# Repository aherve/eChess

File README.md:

# eChess: play online chess, but over the board

https://github.com/user-attachments/assets/bde2e431-92bb-4959-bb7b-e80072c71205

_Demo game against a lichess bot. The phone showcases the game for demo purposes, but isn't actually required to play_

## How it works

- The board is equipped with 64 hall effect sensors, and 64 LEDs.
- The board can communicate via usb to a nodejs program that runs on an embedded raspberry PI with touchscreen
- The program can communicate with both lichess API and the physical board

### Piece detection

The general principle is to hide magnetic hall effect sensors under the board to detect piece presence. White & black pieces have a hidden magnet in them, in different orientations, respectively

Using linear sensors we are then able to detect between 3 distinct states:

- white piece (low voltage)
- black piece (high voltage)
- no piece (~ half the supply voltage)

In addition to the sensors, a 8x8 LED matrix is used to display the opponent's moves on the board. An arduino microcontroller interfaces with an embedded go program to control the LEDs, read the sensors, and communicate with the lichess API.

## Showing the moves

Each square is equipped with a blue LED that can be lit to signal the opponent's move. It's bright enough that we don't miss a move, and discreet enough that it doesn't distract from the game.

## The electronics

For the board to work, is is necessary to:

- read inputs from the program, and light any combination of leds on a 8x8 grid
- read the state of 64 hall effect sensors in near real time, and send the state to the program whenever a change is detected

Since the arduino has a limited number of pins, two 74HC595 shift registers are used to control the LEDs with multiplexing, and an additional 74HC4051 multiplexer is used to control the sensor rows. Each of the sensor outputs are connected to one of the analog inputs of the microcontroller (arduino conveniently has 8 of them).

### The sensor matrix

According to their spreadsheet, the power-on time of the the hall sensors is somewhere from 175μs to 300μs. This is slow enough that we can't use multiplexing to power the sensors. Instead I went for a 8x8 matrix where all of the sensors are always powered. Their input readings are then selected using some BJT transistors whose switch time is in the order of 30ns (so about 8 500 times faster than the sensors power-on time)

<figure>

<figcaption>Details of the sensor matrix, only 4 sensors are shown. Sending <i>QA=1</i>, <i>QB=0</i> and reading <i>A1</i> input would provide a reading of the bottom-right sensor of this diagram</figcaption>
</figure>

### Electronics overview

The three 74HC595 shift registers are chained, and connected to the arduino as follows(only 4 sensors are shown for simplicity):

_complete overview of the electronics. Full kiCad files can be found in the [kiCad](kiCad) directory_

With this setup, [the microcontroller](arduino/arduino.ino) can use multiplexing to control the LEDs and read the sensors in near real time, while using very few pins from the microcontroller.

### The final build

For the build I soldered 64 leds, hall effect sensors, and transistors directly to a wooden board I build and painted. The shift-register ICs are wired to the microcontroller thanks to a custom PCB [ whose files can be found here ](eBoard_pcb)

_soldered pcb with arduino nano, IC sockets and some connectors_

_internal view of the board_

_closeup of the pcb after installation_

## Microconctroller setup

Arduino nano is used. It's cheap, small, and conveniently has 8 analog inputs, which is perfect for this use case.

## workflow

The arduino loop does the following:

1. **Read all the sensors**

   Using multiplexing, read all states from the 64 hall sensors and build a board state from it. If a state change is detected, then we serialize the board state and send it to the computer.

2. **Read the LED input state**

   Read from usb and set the desired LED state

3. **Display the LEDs**

   For each lit LED from the input state, light the corresponding LED on the board, wait 2ms, and turn it off.

Since we are multiplexing the display, the entire loop needs to be _fast_. Fast enough that you don't see any flickering while we are reading 64 sensors and communicating via USB between each LED blink.

## Serializing the position

A chess board has a very convenient size of 8x8, which allows to represent a row with exactly two bytes:

- first byte signals positions of white pieces on row _a_
- second byte signals positions of black pieces on row _a_
- third byte signals positions of white pieces on row _b_
- ...etc until 16 bytes are sent to fully represent the board
- at the end of a serialization, three 255 bytes are sent to signal the end of the transmission. Since (255, 255, 255) would represent at least one row filled with both white _and_ black pieces, there is no ambiguity in the transmission.

This protocol allows the board to send partial states between led blinks, which removes any flickering from the display. The program can wait for a (255, 255, 255) sequence to know that the board state is fully transmitted, and in case of data corruption, it can ignore a broken state, and start over everytime a (255, 255, 255) sequence is detected.

_Example of how a row with 2 white pieces and 1 black piece would be encoded_

## The program

Lastly, the main program is written in go, and communicates with the arduino. It will read both the board state and the game moves from lichess to reconcilate the position, and determine when a move should be played (_i.e._ sent to the server), or when some LEDs should be lit. The user interface is provided by a touchscreen, and everything runs on a raspberry zero.

The code can be found in [the app directory](goapp/)

## Conclusion

I've been playing with this board for quite a while now, and it has been a tremendous experience so far. It's definitely not suited for fast time controls, but lichess only provide their real-time API for rapid & classical time-controls anyway (has to do with anti-cheating measures I believe).

Playing lichess games while looking at a physical board is a delight, and has become my main way of playing chess at home.

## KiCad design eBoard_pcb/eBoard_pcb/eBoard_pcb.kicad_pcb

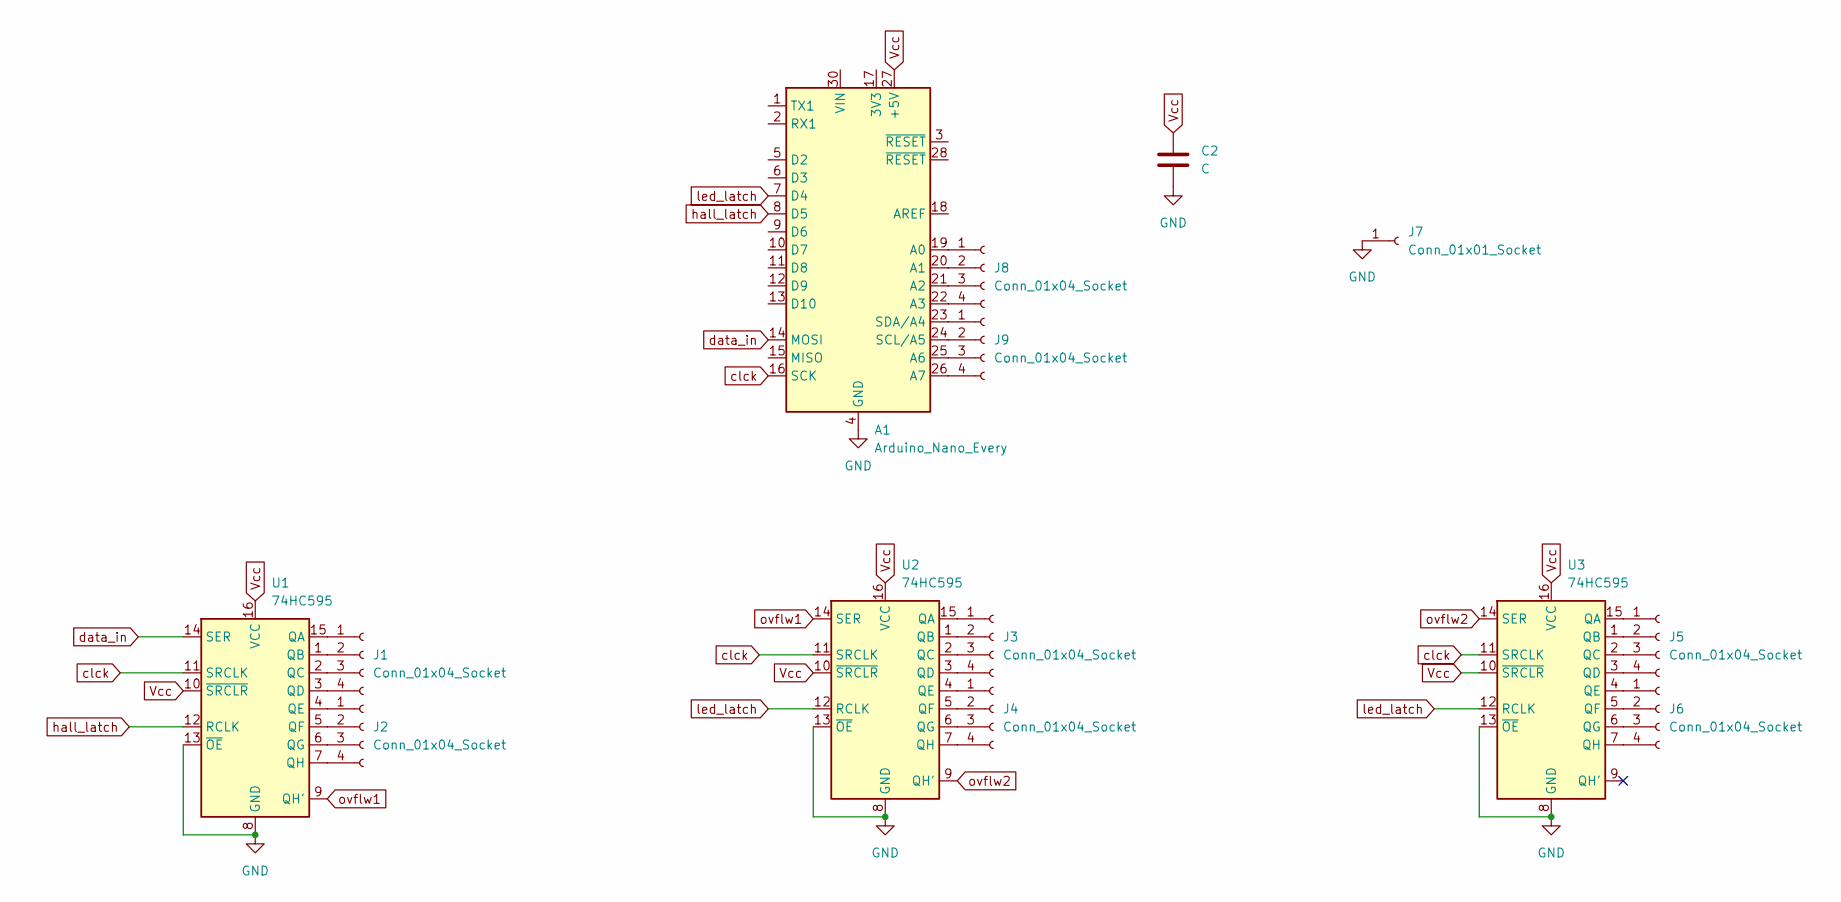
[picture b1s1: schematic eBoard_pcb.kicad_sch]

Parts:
A1: Arduino_Nano_Every; Arduino_Nano
C2: C; C_Disc_D3.8mm_W2.6mm_P2.50mm
J1, J2, J3, J4, J5, J6, J8, J9: Conn_01x04_Socket; JST_PH_B4B-PH-K_1x04_P2.00mm_Vertical
J7: Conn_01x01_Socket; PinHeader_1x01_P2.54mm_Horizontal
U1, U2, U3: 74HC595; DIP-16_W7.62mm_Socket

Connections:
GND: A1.4 (GND), A1.29 (GND), C2.2, J7.1, U1.8 (GND), U1.13 (~OE), U2.8 (GND), U2.13 (~OE), U3.8 (GND), U3.13 (~OE)
unnamed: A1.19 (A0), J8.1
unnamed: A1.20 (A1), J8.2
unnamed: A1.21 (A2), J8.3
unnamed: A1.22 (A3), J8.4
unnamed: A1.25 (A6), J9.3
unnamed: A1.26 (A7), J9.4
unnamed: A1.24 (SCL/A5), J9.2
unnamed: A1.23 (SDA/A4), J9.1
unnamed: J1.1, U1.15 (QA)
unnamed: J1.2, U1.1 (QB)
unnamed: J1.3, U1.2 (QC)
unnamed: J1.4, U1.3 (QD)
unnamed: J2.1, U1.4 (QE)
unnamed: J2.2, U1.5 (QF)
unnamed: J2.3, U1.6 (QG)
unnamed: J2.4, U1.7 (QH)
unnamed: J3.1, U2.15 (QA)
unnamed: J3.2, U2.1 (QB)
unnamed: J3.3, U2.2 (QC)
unnamed: J3.4, U2.3 (QD)
unnamed: J4.1, U2.4 (QE)
unnamed: J4.2, U2.5 (QF)
unnamed: J4.3, U2.6 (QG)
unnamed: J4.4, U2.7 (QH)
unnamed: J5.1, U3.15 (QA)
unnamed: J5.2, U3.1 (QB)
unnamed: J5.3, U3.2 (QC)
unnamed: J5.4, U3.3 (QD)
unnamed: J6.1, U3.4 (QE)
unnamed: J6.2, U3.5 (QF)
unnamed: J6.3, U3.6 (QG)
unnamed: J6.4, U3.7 (QH)
Vcc: A1.27 (+5V), C2.1, U1.10 (~SRCLR), U1.16 (VCC), U2.10 (~SRCLR), U2.16 (VCC), U3.10 (~SRCLR), U3.16 (VCC)
clck: A1.16 (SCK), U1.11 (SRCLK), U2.11 (SRCLK), U3.11 (SRCLK)
data_in: A1.14 (MOSI), U1.14 (SER)
hall_latch: A1.8 (D5), U1.12 (RCLK)
led_latch: A1.7 (D4), U2.12 (RCLK), U3.12 (RCLK)
ovflw1: U1.9 (QH'), U2.14 (SER)
ovflw2: U2.9 (QH'), U3.14 (SER)

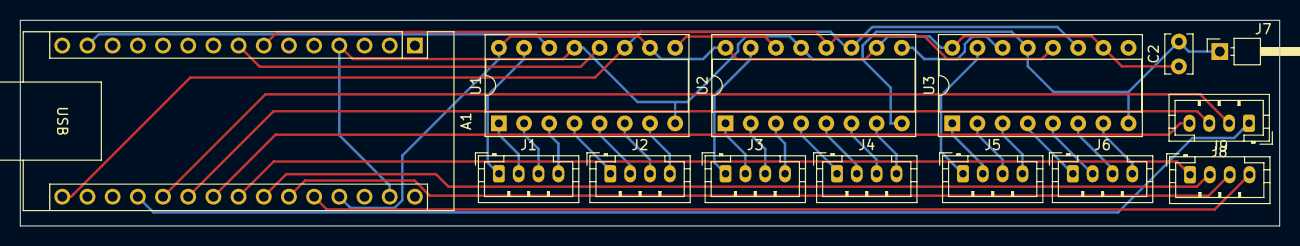
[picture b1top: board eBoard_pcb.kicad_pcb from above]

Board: 2 copper layers, 127.0 x 20.7 mm, 14 parts (0 on the bottom side), 40 nets.

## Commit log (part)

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2024-12-28 initial commit: move files from private to public repo
2024-12-28 rename dir
2024-12-28 add demo video
2024-12-28 test video
2024-12-28 test2
2024-12-28 try with mp4
2024-12-28 hall test
2024-12-28 iamge
2024-12-28 preview
2024-12-28 wipwip
2024-12-28 test
2024-12-28 arduino workflow
2024-12-28 moar
2024-12-28 something
2024-12-28 let's go
2024-12-28 Readme (#1)
    let's go
2024-12-28 few fixups
2024-12-28 testing
2024-12-28 minor tweaks
2024-12-28 typo fix
2024-12-28 caption
2025-01-02 fiddling around with blessed
2025-01-02 fun fun fun
2025-01-02 vitest to debug gui
2025-01-02 progress
2025-01-02 raw clock
2025-01-02 fixup! raw clock
2025-01-03 fix game seeking
2025-01-03 wip sounds
2025-01-03 fix sounds
2025-01-03 remove vitest cache
2025-01-03 add some buttons
2025-01-03 fix sounds for real
2025-01-03 this is playable
2025-01-03 cancel seek when a game is found
2025-01-03 gui is working
2025-01-04 use caffeinate to run script and prevent laptop from going to sleep
2025-01-04 add chat
2025-01-04 prevent gui accumulation
2025-01-05 change presets
2025-01-06 cleanup
2025-01-06 Gui (#2)
    * fiddling around with blessed
    * fun fun fun
    * vitest to debug gui
    * progress
    * raw clock
    * fixup! raw clock
2025-01-08 tsc, compile to js for better inter operability
2025-01-08 list ports
2025-01-08 add port filtering for rpi
2025-01-09 testing sounds
2025-01-10 visual start & end sequences
2025-01-14 disable sound
2025-01-14 gui tweaks
2025-01-15 simplify text
2025-01-15 more tweaks
2025-01-16 logging
2025-01-16 try and debounce arduino board state
2025-01-16 fixup! try and debounce arduino board state
2025-01-16 raise threshold to avoid flickering when using RPI instead of a macbook
2025-01-24 add extension image
2025-01-24 more photos
2025-01-24 readme update
2025-02-15 testing other formats
2025-02-15 add restart command
2025-02-15 remove sounds
2025-05-04 can stream lichess moves
2025-05-04 trying ui
2025-05-04 stream board events
2025-05-04 board state updates
2025-05-04 still wip
2025-05-04 renaming
2025-05-05 works, but with a weird transposition
2025-05-05 better
2025-05-05 minor cleanup
2025-05-05 fixes
2025-05-05 detect valid move
2025-05-05 play move stub
2025-05-05 works, can play a game
2025-05-05 ready for using the ui
2025-05-05 needs ui
2025-05-06 ui wip
2025-05-06 add time anchor
2025-05-06 seeking page
2025-05-06 ui progress
2025-05-06 ready to play, probably
2025-05-06 it works
2025-05-06 styling
2025-05-06 padding on seek buttons?
2025-05-06 some styling
2025-05-06 maybe fixes
2025-05-07 remove stupid changes
2025-05-07 board, candidate move
2025-05-07 refactoring game
2025-05-07 concurrency safety wip
2025-05-07 should be safe
2025-05-07 maybe a little bit less mutexes
2025-05-07 minor tweak
2025-05-07 another bugfix
2025-05-07 fixup! another bugfix
2025-05-07 perf improvement?
2025-05-08 improved performances
2025-05-08 bugfix
2025-05-08 also reset chess game on termination
2025-05-10 promotion modal ok
2025-06-04 display opponent on top, current player in the middle
2025-06-04 fix typo
2025-08-30 deprecate old node app
2025-08-30 fixup! deprecate old node app
2025-09-20 display opponents draw offer instead of their name
2025-09-20 fix secret reading
2025-09-20 fixup! fix secret reading
2025-10-21 wip: prepare board events for display between games
2025-10-21 fixup! wip: prepare board events for display between games
2025-10-21 working
2025-10-21 middle point?
2025-10-23 add tons of loggers
2025-10-23 fixup! add tons of loggers
2025-10-23 try some changes
2025-10-23 trying stuff
2025-10-23 more debug
2025-10-23 moar logs
2025-10-23 finally a real fix candidate
2025-10-23 remove debug loggers
2025-12-14 rebased
2026-01-02 update sensivity
2026-01-02 update sensivity for raspberry controller
2026-01-03 more tweaking
2026-01-30 update on auto-abort
2026-01-30 do not autoabort classical games (for now)
